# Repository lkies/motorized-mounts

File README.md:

# DIY Motorized Mirror Mounts

_Lorenz Kies <[lorenz.kies@aei.uni-hannover.de](mailto:lorenz.kies@aei.uni-hannover.de)>_

_I designed this project during my employment as a research assistant at the Institute of Gravitational Physics at Leibniz University Hannover; it is therefore intellectual property of my employer, but I have been given permission to share it under an open source license._

## Introduction

Motorized mirror mounts for guiding laser beams are already an established commercial product, but their pricing makes them unreasonable for basic automation tasks for most people. This means they are mostly reserved for applications where remote control or precise repeatable positioning is required. This is why I decided to develop a low-cost alternative for cheap automatic alignment of optical experiments. Most commercial offerings start at around $1000 per axis (including the driver), or around $4000 for a full 4-axis system required for most alignment problems. In contrast, my design can be build for under $100 for a full set, so less than $25 per axis, relying mostly on standard components and 3D printed parts. Despite the low cost, the actuator performance is competitive with lower-end commercial products and more than sufficient for most automatic alignment problems.

If you want to simply build the actuators, go to the [Instructions](#instructions) chapter. Following that, I discuss some of the [mechanical](#mechanical-design) and [electrical](#electrical-design) design considerations I made, that may be of interest to you, if you want to modify the designs. Finally, I discuss the [characterization](#characterization) experiments and metrics used to evaluate the performance of the actuators.

## Table of Contents

- [Introduction](#introduction)
- [Instructions](#instructions)
  - [Parts List](#parts-list)
  - [Actuator Assembly Instructions](#actuator-assembly-instructions)
  - [Electronics Setup](#electronics-setup)
  - [Firmware Setup](#firmware-setup)
  - [API / Software Setup](#api--software-setup)
- [Design Considerations](#design-considerations)
  - [Mechanical Design](#mechanical-design)
  - [Backlash and Hysteresis Compensation](#backlash-and-hysteresis-compensation)
  - [Electrical Design](#electrical-design)
- [Characterization](#characterization)
  - [Minimal Incremental Motion](#minimal-incremental-motion)
  - [Unidirectional Repeatability](#unidirectional-repeatability)
  - [Nonlinearity](#nonlinearity)
  - [Backlash](#backlash)
  - [Backlash Variation](#backlash-variation)
  - [Interpretation](#interpretation)
  - [Results](#results)

## Instructions

These are the instructions to build the `pancake-direct-v2` design, which is the recommended design. The other designs are mostly included for completeness' sake, if you want to build them you will have to figure it out yourself from the CAD files.

### Parts List

To build a set of **four actuators** on two **mirrors**, you will need the following parts:

| Electronic Parts | Quantity |
| - | - |
| [NEMA 14 Pancake Stepper Motor](https://www.omc-stepperonline.com/de/e-serie-runden-nema-14-bipolar-0-9deg-8ncm-11-33oz-in-1-0a-36x17mm-4-draehte-14re07-1004vrn) | 4 |
| [TMC2208 StepStick V1.2](https://aliexpress.com/item/33045459259.html) | 4 |
| [Makerbase MKS DLC32 MAX](https://aliexpress.com/item/1005008204547315.html) | 1 |
| [19V 5A Power Supply (5.5mm x 2.5mm socket)](https://de.rs-online.com/web/p/steckernetzteile/2552119) | 1 |
| [Cat7 U/FTP 2m Ethernet Cable](https://de.rs-online.com/web/p/ethernetkabel/2660713) (optional) | 2 |
| [Adapter-Board-Stepper](electrical/adapter-board-stepper) (optional) | 2 |
| [Adapter-Board-Controller](electrical/adapter-board-controller) (optional) | 2 |
| [RJ45 Socket](https://de.rs-online.com/web/p/ethernet-steckverbinder/3316443?searchId=30a561ef-d51f-4305-b438-8268e3811f80) (optional, for adapter boards) | 4 |

The links for the motors, motor drivers, and driver board are not affiliate links, they are simply the first results I found. All parts are also offered by many other suppliers. If you can not find the exact same model, you should also be able to use similar parts that perform the same function.

There are a lot of other CNC driver boards out there, many of them ESP32 based. Alternatively, it is also not too difficult to build one yourself. Similarly, you can also use different stepper drivers like the TMC2209, DRV8825 or A4988. Most stepsticks are pin compatible at least to the extent required for basic operations. If you choose to buy TMC2208 stepsticks, I recommend getting the white v1.2 version, there are many step stick designs available and some of them seem to have weird factory side configurations. Although 15V and 3.5A should technically be enough for the power supply, I recommend staying on the safe side and getting a more powerful one like the one specified. If you do not have the capabilities to manufacture PCBs, you can also buy [RJ45](https://de.aliexpress.com/item/1005004520312413.html) breakout boards instead of the custom adapter boards, or skip the Ethernet cables entirely.

| Mechanical Parts | Quantity |
| - | - |
| [MDI-HS Mirror Mount](https://www.radiant-dyes.com/index.php/products/optomechanics/high-stable-mirror-mounts/131-mdi-hs) | 2 |
| DIN 912 M2x16mm | 4 |
| DIN 934 M2 Nuts | 4 |
| DIN 912 M3x6mm | 8 |
| DIN 912 M4x12mm | 4 |
| DIN 912 M6x16mm | 2 |

In most cases, it is not necessary to use DIN 912 of these exact lengths, just use whatever is available.

| 3D Printed Parts | Material | Quantity |
| - | - | - |
| [`gear-grip.stl`](mechanical/pancake-direct-v2/gear-grip.stl) | PETG | 4 |
| [`screw-grip.stl`](mechanical/pancake-direct-v2/screw-grip.stl) | TPU 95A | 4 |
| [`fastener.stl`](mechanical/pancake-direct-v2/fastener.stl) | PETG | 4 |
| [`mount-plate.stl`](mechanical/pancake-direct-v2/mount-plate.stl) | PETG | 2 |
| [`mount-stem.stl`](mechanical/pancake-direct-v2/mount-stem.stl) | PETG | 2 |
| [`adapter-board-mount.stl`](mechanical/adapter-board/adapter-board-mount.stl) (optional) | PETG | 2 |
| [`driver-board-case-lower.stl`](mechanical/driver-board-case/driver-board-case-lower.stl) (optional) | PETG | 1 |
| [`driver-board-case-upper.stl`](mechanical/driver-board-case/driver-board-case-upper.stl) (optional) | PETG | 1 |

Other materials like PLA instead of PETG or other flexible filaments instead of TPU 95A will probably also work, this is just what I used. If you have access to a laser cutter, you can also cut the [`mount-plate.dxf`](mechanical/pancake-direct-v2/mount-plate.dxf) out of 2.5mm to 3mm thick acrylic. This is a bit stiffer and looks nicer.

### Actuator Assembly Instructions

1. Crimp a plug to the wires, make sure that the first two wires are one phase and the second two wires are the other phase, do not mix them. The polarity and positioning of the phases determine the rotation direction, but this does not really matter for most applications.
2. Insert M2 nut into `fastener`. If it does not fit, heat the nut using a lighter or soldering iron. If it does not sit tight, heat the plastic and press it together around the nut. Alternatively, hose clamps might also work well for this, but I did not test that.
3. Put the `gear-grip` on the output gear of the motor. If it is too tight, slightly bend the two halves apart. The part has a chamfer on one side that should also help with this.
4. Put the `screw-grip` on the `gear-grip`, make sure that the shallow slots in the `gear-grip` align with the shallow notches on the `screw-grip`.
5. Push the `fastener` onto the `gear-grip`, if it is too tight, slightly bend the `fastener` apart. The `fastener` has a chamfer that should mate with a very thin shoulder on the `screw-grip` to help with the alignment.
6. Before tightening the fastener, use a knife (or another thin piece of metal) to make a small gap (~0.5mm) between the motor and `gear-grip` to avoid unnecessary friction between the two.
7. Tighten the fastener using an M2x16mm screw. If the M2 nut in the `fastener` breaks free, use pliers to hold it in place while tightening.
8. Repeat steps 1-7 for the other three motors.
9. Fasten the `mount-plate` to the `mount-stem` using two M4x12mm screws. Repeat for the other mount.
10. Place two motor assemblies on their back with the wires facing inwards. (Not really necessary, but it looks nicer in my opinion.)
11. Fasten the `mount-plate` / `mount-stem` assembly onto the two motors using four M3x6mm screws. Repeat for the other mount.
12. Put a M5x16mm screw through the hole of the mirror mount that is **not** used for screwing it to its foot. Screw it in so that the head is roughly in the center of the optical axis.
13. Place the whole mirror actuator assembly onto the mirror mount and tighten the M5 screw. Repeat for the other mount. When setting up the mounts as part of a setup, I recommend doing the placement and rough alignment without the actuator assembly attached, and only attaching it for fine automatic alignment.

### Electronics Setup

1. For each of the red DIP switches between the stepstick slots, switch them all to the down/off position to select 8 microsteps per full step.
2. Plug the stepsticks into the driver board. Most stepsticks have some of the pins labeled _somewhere_ so you know which way around to plug them in.
3. If you built the adapter boards, plug them in. Beware, many CNC driver boards have two sockets for the y-axis, make sure to skip the second one.
4. **With the motors disconnected**, connect the power supply and adjust driver current reference voltage as described in the ["Motor Current Setting"](https://wiki.fysetc.com/docs/TMC2208#Motor%20Current%20Setting) section. I set it to 800 mV which indicates an RMS current of 800 mA. This may be slightly different for other stepstick designs. The drive current is a tradeoff between torque and heating. With a larger current, the motor can produce more torque and consequently move at higher speeds. However, it will also heat up faster and reach higher temperatures. The TMC2208 has an auto power-down feature that reduces the current during standstill. If you have this feature and use the motors infrequently enough, you may get away with higher currents without overheating. The motors are rated for 1.0 A per phase, so with 800 mA, should be on the safe side.
5. Attach the driver board adapters to the driver board and put the assembly in the case and close it with six DIN 912 M3x20 screws.

### Firmware Setup

1. Install Python in your preferred way.
2. Install [`esptool`](https://pypi.org/project/esptool/) for example using pip:

    ```shell
    pip install esptool
    ```

3. Download the [firmware image](firmware/firmware.bin).
4. Erase the flash memory of the controller board using:

    ```shell
    esptool --chip esp32s3 erase_flash
    ```

    If you have multiple serial devices connected, you may also need to specify the port using `--port COM[X]` on Windows or `--port /dev/ttyUSB[X]` on Linux.

5. Flash the image using:

    ```shell
    esptool --chip esp32s3 write_flash 0x0 firmware.bin
    ```

    The same note about the port applies here as well.

If you are using a different board, you will need to configure the correct pins and potentially switch the build system different architecture. You can find more details on this in the [`firmware` directory](firmware).

### API / Software Setup

1. Install Python in your preferred way.
2. Install the API package from source control using pip:

    ```shell
    pip install git+https://github.com/lkies/motorized-mounts.git#subdirectory=api
    ```

3. Control the steppers through a `StepperBoard` instance:

    ```python
    from stepper_board import StepperBoard, RpcClient, SerialBLS

    # the default baudrate of ESPs is 115200
    with SerialBLS.connect("COM[X]", 115200) as bls:
        # create proxy instance of stepper board connected to serial port
        steppers = StepperBoard(RpcClient(bls))

        # configure speed, acceleration and compensation settings
        # only needed once, the settings are saved the board's non-volatile memory
        for i in range(4):
            steppers.set_max_speed(i, 500)
            steppers.set_max_accel(i, 1e5)
            steppers.set_backlash(i, 10) # in case you want to use backlash compensation
            steppers.set_hysteresis(i, 30)
            steppers.set_compensation("hysteresis")

        # enables the stepsticks
        steppers.set_enabled(True)

        # move stepper 0 to position 1000 microsteps
        steppers.move_to(0, 1000)

        # move multiple steppers simultaneously
        steppers.move_to_vec([10, 20, 30, 40], "joint_max") 
    ```

The configuration only needs to be done once, the settings are stored on the chip's non-volatile memory and it is automatically reloaded at startup. From the characterization measurements, the backlash compensation should be about 10 microsteps at 8 microsteps per full step. The hysteresis compensation needs to be at least as large as the maximum backlash, in this case, greater than about 15 microsteps. To be on the safe side, we choose 30 microsteps. A larger hysteresis correction will cause more unnecessary extra movement, but at these small scales, it does not really matter. The best performance is achieved with hysteresis compensation, so unless you have a good reason to use backlash compensation, I would recommend using hysteresis compensation.

You can find more information about the driver boards behavior in the [`api` directory](api).

_Please consider providing feedback on the build process if you end up replicating this design so that we can optimize the instructions and the design itself. Have Fun!_

## Design Considerations

### Mechanical Design

Building a stable and robust mirror mount is not a trivial task. That is why I did not do it and instead built the design around the [MDI-HS](https://www.radiant-dyes.com/index.php/products/optomechanics/high-stable-mirror-mounts/131-mdi-hs) series mirror mounts from Radiant Dyes. They have proven themselves as reliable and stable mirror mounts in our labs. They also have slightly larger thumbscrews than other mounts, which is helpful in reducing coupling slack between them and the motor.

For the motors, I experimented with two different types of stepper motors: the extremely cheap 28BYJ-48 geared stepper motors and the slightly more expensive [Nema 14 Pancake motors](https://www.omc-stepperonline.com/de/e-serie-runden-nema-14-bipolar-0-9deg-8ncm-11-33oz-in-1-0a-36x17mm-4-draehte-14re07-1004vrn) (400 step/rev version). The 28BYJ-48 motors are normally unipolar stepper motors, but they are not too difficult to [modify for bipolar operations](https://ardufocus.com/howto/28byj-48-bipolar-hw-mod/). This has two advantages: first, bipolar operation is not limited to using half the coil windings, which means more torque. Second, and much more importantly, it is much easier to get good microstepping drivers for bipolar motors, such as the TMC2208. This is very important because the excess vibration caused by bad drivers causes a lot of problems with sensitive optical experiments.

One simple method for increasing the actuation resolution of an actuator is to use a gear reduction. However, this may not always lead to better performance since the gearing also introduces backlash and other hysteresis-like effects. To investigate this, I designed a geared and a direct drive version for both motors. Typically, gearboxes, especially stiff metal gears, are intentionally designed with some slack to prevent jamming and allow for lubrication, but this also means that they will have backlash. Without this play, even tiny manufacturing tolerances can reduce the slack "below zero" which then requires strong deformation forces to move past, if possible at all. This is not as critical in plastic gears, which allow for more deformation. In fact, we can deliberately introduce radial compliance in the gear, which then allows us to preload them without the risk of jamming and excessive required forces to move. With this, we can effectively eliminate backlash, but the compliance itself may introduce other hysteresis-like effects.

Another challenge is to provide a reliable coupling between the motor and the mount. While a form fit is generally good for preventing slippage, it requires precise manufacturing to match the mating part. In addition to that, the stiff coupling requires the axis of the mount to be very well aligned with the axis of the motor, otherwise the mechanism may not be able to move freely. Because of these reasons, I choose to use a friction fit with TPU 95A, providing the required compliance. This has a few advantages, firstly, the compliance allows for slight radial misalignments by deforming. The knurled knob provides good grip for torque transfer while still allowing for some axial slip to deal with the screw moving in and out of the mount as it is actuated. And finally, it is easy to manufacture on most 3D printers and does not require additional elements like grub screws. The major disadvantage is that there will be additional hysteresis-like effects. In practice, this does not seem to be very severe, although it is possible that it is currently a limiting factor on the minimal incremental motion.

### Backlash and Hysteresis Compensation

While there is only one way for an actuator to be "perfect", i.e. a simple linear mapping from desired position to actual mirror orientation, there are many ways in which an actuator can be imperfect. Here is a list of the types of imperfections investigated and possible compensation approaches. You can find more details about how we characterized them in the [Characterization](#characterization) section.

- Minimal Incremental Motion: This is the smallest unidirectional change in position that the actuator can reliably produce. Changes in input that are smaller have no meaningful effect on the output due to digital resolution limits, stick-slip effects or limitations in the drive train.
- Backlash: It is commonly defined as "the maximum distance or angle through which any part of a mechanical system may be moved in one direction without applying appreciable force or motion to the next part in mechanical sequence." For our purposes, we can define it as the additional change in input we need to apply after a direction change before the output starts to change. If this is consistent, it can be compensated for by adding that amount to the input when changing direction.
- Backlash Variability: If the backlash is not consistent over the actuator's range of movement, it can not be compensated for with simple backlash compensation. However, if it is consistent for a given position, we can compensate for it by always approaching the desired position from the same direction. With this approach, we can also compensate for any other hysteresis-like effects, so we will call it hysteresis compensation as opposed to the simple backlash compensation. Hysteresis compensation is generally more robust and leads to better accuracy because it compensates for more imperfections and does not require precise knowledge of the backlash. However, it is slower since it requires extra movement to approach the desired position from the correct direction.
- Macroscopic Nonlinearity: Besides the small-scale nonlinear behavior described by the minimal incremental motion, there may also be macroscopic nonlinearities due to non-ideal components in later stages of the transmission. These could be compensated for by calibrating them out, but this is generally not necessary for automatic alignment applications where precise repeatable movement is much more critical.

### Electrical Design

The stepper motors are a crucial part for providing precise, repeatable actuation. To get the best performance out of them, it is important to use good stepper drivers. I chose the TMC2208 drivers because of their quiet and vibration free stealth chop mode to avoid disturbing sensitive optical experiments, but other drivers might also be good enough and are usually pin compatible if integrated onto a stepstick. To drive them I used an ESP32 (old or S-series) because of their high resolution timers and established ecosystem. While it is not too hard to design a PCB that connects the microcontroller to the four stepsticks, it is superfluous because this kind of problem has been solved many times before for CNC machines, 3D printers and laser cutters. There are a lot of these boards out there, and quite a few of them even use the ESP32 based controllers. I selected the Makerbase MKS DLC32 MAX V1.2 because it is compact and cheap (<20€ on AliExpress) and has the required four stepper driver slots and ESP32s3 controller. Sadly, the schematics are not open source, but the [pinout](https://github.com/user-attachments/files/19184922/MKS.DLC32.MAX.V1.0_002.PIN.pdf) can be found online.

I wrote my own firmware that implements speed and acceleration limits, as well as backlash and hysteresis compensation, with a simple JSON-based serial interface to control it. But it might be interesting to investigate using established software like [GRBL](https://github.com/grbl/grbl) to simplify the project even further.

While the motors I used do not require much power, I would still recommend using a power supply with more than 15V. At high speeds, the inductance becomes the limiting factor in how much current can flow. If the driver has a higher voltage supply, it can change the current through the inductor faster to maintain reasonable torque at high speeds. But be careful setting the current limit on the drivers, they can easily overheat and potentially damage the 3D printed parts.

Since you will most likely not want to mount the controller board on your optical table, you will need to extend the motor wires somehow. For this, I recommend using Ethernet cables. With four twisted pairs, a single Ethernet cable can drive two stepper motors, enough for the two axes of a single steering mirror. Another advantage of using Ethernet cables is that they also shield the individual motor wire pairs preventing electromagnetic interference from the comparatively high drive currents. While more shielding might sound attractive, especially considering the current going through these wires, I still recommend using U/FTP cables because they are typically much more flexible than cables with overall shielding. To go from the driver board to RJ45 and back at the mirrors, we use custom adapter boards, but you can also buy RJ45 breakout boards if you do not have the capability to make your own.

## Characterization

To measure the performance of the actuators, we use one simple experiment and multiple evaluations to extract the quantities of interest from the data. The experimental setup is very straightforward, we shine a laser beam at the mirror of the mount to be evaluated and then measure the changes in position on a screen. The position which is approximately proportional to the change in mirror angle is measured using the difference voltage of a four quadrant photodetector, while this is not linear in the position, the nonlinearity is easy to calibrate out. We then move the actuator back and forth multiple times and record the input and measured output position. After each movement, we wait for 100 ms for the mount and table to settle to get as precise a measurement as possible. All performance metrics are then derived from this data.

Example code for computing the quantities can be found in the [plotting notebook](images/plots/plots.ipynb). The actual code used is slightly different and can be found in the [evaluation module](characterization/evaluation.py). To better illustrate the individual effects, the example plots shown are based on simulated data which is also generated in the plotting notebook.

### Minimal Incremental Motion

In a loose sense, the minimal incremental motion is the smallest change in input, that reproducibly leads to a change in output. To quantify it we look at small segments of the unidirectional travel, where other nonlinearities are negligible. We compute the mean expected movement using a unity slope linear regression line and then look at the distribution of the residuals. Ideally, the span of the distribution i.e. max - min then gives us the minimal change in input that we need to apply to get a reliable change in output. In practice, the measurements are subject to noise and so maximum and minimum values are most likely outliers which are not representative of the expected performance. We can mitigate this by only looking at the inner $x$ percent of values. For example if we want to take the inner 95% of values we use the 2.5th and 97.5th percentile instead of the minimum and maximum.

We can get estimates of the confidence intervals by bootstrapping the distribution of residuals.

<image src="images/plots/min_increment.png" alt="Minimal Incremental Motion Plot" width="400px"/>

The plot shows minimal incremental motion limited by stick slip effects. For most small changes in input, the system "sticks" and the changes in output are purely noise. Once the input change is large enough, the system "slips" and the output changes suddenly. Because of this, the system can not be controlled at scales finer then the "steps" of the slips.

### Unidirectional Repeatability

In addition to the mostly consistent stick-slip effects that limit the minimal incremental motion, there may be other randomized effects that cause the actuator's output to differ between multiple repetitions of the same input. We call this unidirectional repeatability. This is in contrast to bidirectional repeatability, which is usually limited by backlash and backlash variation. We determine it by examining the peak-to-peak deviation in output across multiple repetitions of the same input, while accounting for movement direction. And again, to account for measurement noise, we do not use the maximum and minimum values but instead use percentiles for greater robustness against noise and outliers. By only comparing against points with the same input and direction as opposed to a linear regression line, this metric is independent of nonlinearity or backlash.

<image src="images/plots/unidirectional_repeatability.png" alt="Unidirectional Repeatability Plot" width="400px"/>

Moving through the same segment multiple times, we see that the output randomly ends up in slightly different positions, limiting the achievable accuracy.

### Nonlinearity

Ideally, after accounting for backlash and minimal incremental motion, there should be a linear relationship between input and output position. In practice, this might not be the case due to manufacturing tolerances across various parts of the drive train. To quantify this, we look at motion across a large segment of the travel and compute the residuals to a linear regression. Similar to minimal incremental motion, instead of directly using the minimum and maximum values, we use percentiles to mitigate the effects of outliers.

<image src="images/plots/nonlinearity.png" alt="Nonlinearity Plot" width="400px"/>

The input-output relationship is not perfectly linear. A user or application that assumes linear behavior will see a systematic deviation from the expected output corresponding to the nonlinearity.

### Backlash

In general, hysteresis is the dependence of a system's state on its history. In the context of actuators, this usually means whether we previously moved the actuator in the same direction or not. In more complicated cases, the behavior may also depend on how long ago the last change in direction was. The dominant source of hysteresis effects in mechanical systems is usually backlash. It is the consequence of play in the force-transmitting elements of the actuator. When we change direction, parts with play need to move through a dead zone before they make contact again and start transmitting force. We defined backlash as the additional movement we need to apply to the actuator after changing direction before the output begins to change.

To determine the backlash from measured data, we can perform a virtual backlash compensation during measurement post-processing. For this, we split all movement segments into forward and backward motion. Then we then shift the recorded input values of the backwards motion by the amount of backlash to compensate for. Finally, we delete the datapoints in the dead zone after changes in direction. We define the backlash as the compensation value that maximizes overlap between the forward and backward segments. In the process, we also get backlash-compensated data that we can use for other evaluations.

Alternatively, we can also determine the backlash as the negative of the signed integral of the hysteresis loop in the input-output space relative to the maximum change in output position (i.e. change in input minus backlash). The advantage of this method is that it does not require a metric to compute the overlap between forward and backward segments. The downside is that we always need to integrate over full hysteresis loops to get valid results. Additionally, we also do not get backlash compensated data for other evaluations.

In both of these evaluations, we compute the backlash in terms of the input position. However, we are usually interested in the backlash in terms of output position. For this, we just multiply it by the input-output proportionality.

It is important to note that it is a matter of convention that we choose the forward direction to be the true direction and the backward direction to be the one affected by backlash. We could just as easily select the backward direction to be the true direction or any mix of the two and split the backlash compensation between the two. However, there is an output offset between the different conventions. The driver board considers the forward direction to be the true direction and applies the backlash compensation to the backward direction, so we stick to this convention for consistency.

We can get confidence intervals by computing the backlash for each cycle individually and then using standard t-statistic-based confidence intervals.

<image src="images/plots/backlash.png" alt="Backlash Plot" width="400px"/>
When changing direction, there is a dead zone before the output starts to change again. This means that the output position is consistently to hight when moving backwards. By shifting the recorded input values for all backwards motion and cutting out the dead zone after direction changes, the forward and backward trajectories overlap again.

### Backlash Variation

While constant backlash is not too difficult to compensate for by adding a constant bias after a direction change, this does not work for variable backlash. In that case, compensating for an average backlash will lead to overcompensation in some cases and undercompensation in others. Quantifying this is somewhat messier than the other metrics, as we need a way to determine the local backlash. To get a reasonable estimate of the local backlash, we need to be able to determine the input deviation between the forward and backwards trajectories for the same output positions. To provide a balance between resolution and smoothing, we interpolate using a Gaussian kernel with a bandwidth equal to the average spacing between consecutive outputs. We then collect all deviations between forward and interpolated backwards or backwards and interpolated forward trajectories. From these deviations we can then again compute lower and upper quantiles to get noise-robust estimates of the differences between maximum and minimum values.

<image src="images/plots/backlash_variation.png" alt="Backlash Variation Plot" width="400px"/>

The backlash is not consistent across the range of movement. After compensating for the average backlash, the range with small backlash is overcompensated and the range with large backlash is undercompensated. This leads to a systematic deviation from the expected output that depends on the position of the actuator.

### Interpretation

An obvious question that arises when looking at these metrics and comparing different motors is, which of these metrics actually matter? The annoying answer here is, it depends on the application and the compensation mode or lack thereof, that is used. For this, we need to introduce the terms of accuracy and precision, which we will call repeatability, to avoid confusion with accuracy. Accuracy describes the deviation of the _expected_ output (i.e., averaged across many iterations) from the true (linear) relation, or, in a looser sense, whether the average output is correct. Precision or repeatability describes the deviation of individual measurements between multiple repetitions of the same input, or in a looser sense, is the actuator consistent. So accuracy or lack thereof is a matter of systematic errors, while repeatability is a matter of random errors. Even though backlash and backlash variation are technically deterministic, we will treat them as random errors for measures of repeatability, as they can appear random to a user or algorithm that is not aware of the history of the actuator.

With this, we can specify the expected performance for different compensation modes. The specified values are bounds for worst-case deviations, discounting errors from noisy measurements and extreme outliers (because we used percentiles instead of maximum and minimum values). We assume that the backlash compensation is applied with the median backlash (between minimum and maximum variation) and that the hysteresis compensation is applied with at least the maximum backlash.

| Compensation Mode       | Remaining (In-)Accuracy                      | Remaining (Un-)Repeatability                                                              |
|-------------------------|----------------------------------------------|-------------------------------------------------------------------------------------------|
| None                    | Backlash + Backlash Variation + Nonlinearity | Backlash + Backlash Variation + Unidirectional Repeatability + Minimal Incremental Motion |
| Backlash Compensation   | Backlash Variation + Nonlinearity            | Backlash Variation + Unidirectional Repeatability + Minimal Incremental Motion            |
| Hysteresis Compensation | Nonlinearity                                 | Unidirectional Repeatability + Minimal Incremental Motion                                 |

If we define the ground truth to lie between the most extreme positive and negative deviations, the actual accuracy and repeatability will be half the values specified.

Depending on the application, either the accuracy or repeatability may be more important. For example, for auto-alignment applications using hysteresis compensation, the nonlinearity will effectively distort the observed figure of merit in terms of the input. As long as this distortion is small enough, this should not matter to the optimizer which mostly cares about repeatability.

Overall, the best performance is achieved with hysteresis compensation, and it should therefore be the default choice for most applications. The only downside compared to backlash compensation is that it leads to additional movement to always approach the desired position from the same side. This makes actuation slower, especially if most movements are smaller than the hysteresis compensation value.

### Results

At the time of performing the characterization measurements, we also had two commercial models from Newport available, which they had kindly lent us for evaluation. The [TRA6CC](https://www.newport.com/p/TRA6CC) designated as `newport-dc` is a closed loop DC motor, the [TRA6PPD](https://www.newport.com/p/TRA6PPD) designated as `newport-stepper` is an open loop stepper motor based design.

The characterization experiments were performed with the following parameters:

- Short evaluation range: $5\text{ mdeg}$ (Used for minimal incremental motion)
- Long evaluation range: $50\text{ mdeg}$ (Used for all other evaluations)
- Number of cycles for short stroke high resolution measurements: $10$
- Number of cycles for long stroke measurements: $5$
- Evaluation quantile for noise robust min max estimates: $95\%$ (i.e. 2.5th and 97.5th percentiles)
- Confidence interval: $95\%$ (rounded up to larger deviation for asymmetric intervals)
- Bootstrap samples: $10 000$

The actual stroke lengths varied between the different motors, but they were all larger than the evaluation range.

| Actuator Model    | 95% min. inc (µdeg)   | 95% uni. rep. (µdeg)   | 95% nonlin. (µdeg)   | backlash (µdeg)   | 95% BL var. (µdeg)   |
|:------------------|----------------------:|-----------------------:|---------------------:|------------------:|---------------------:|
| `cheap-geared`    | 521 ± 27              | 490 ± 19               | 1034 ± 23            | 2763 ± 116        | 507 ± 19             |
| `cheap-direct`    | 490 ± 39              | 2014 ± 131             | 923 ± 44             | 4420 ± 590        | 2007 ± 132           |
| `pancake-geared`  | 445 ± 18              | 1144 ± 25              | 803 ± 40             | 1620 ± 768        | 1154 ± 20            |
| `pancake-direct`  | 503 ± 33              | 614 ± 21               | 613 ± 20             | 1543 ± 170        | 622 ± 20             |
| `newport-dc`      | 285 ± 15              | 534 ± 18               | 587 ± 18             | 10692 ± 105       | 539 ± 17             |
| `newport-stepper` | 298 ± 16              | 441 ± 17               | 533 ± 16             | 10049 ± 63        | 459 ± 14             |

The uncertainty estimates provided are purely derived from statistical data and do therefore not account for systematic errors. For example, the `cheap-direct` instance was probably built using an unusually bad motor since it has significantly more backlash variation and repeatability than the geared version. Even with a perfect gear reduction, the direct-drive version should only be three times as bad as the geared version.

It is interesting to note that all DIY designs have roughly the same minimal incremental motion. This suggests that it is not limited by the motor or gear reduction but rather by the parts they share in common. The most likely candidate for this is the TPU friction fit coupling, but it is also possible that it is the threading in the mirror mount. To put this into context, $500\text{ µdeg}$ in rotation corresponds to about $270\text{ nm}$ of screw translation, which is already impressively small for something based on metal sliding on metal.

Overall, the `pancake-direct` design has the best overall performance of the DIY designs, while also being the simplest to build. It is still beaten by the commercial models in terms of minimal incremental motion, but it has very similar performance in terms of repeatability, nonlinearity and backlash variation. The backlash itself is significantly better than the commercial models, although this does not necessarily provide an advantage in practice since backlash is easily compensated. However, it does make hysteresis compensation more feasible since the extra movement required to approach the desired position from the correct direction is smaller. It is worth noting that the Newport motors were at a slight advantage due to their larger mirror mount lever of $40\text{ mm}$ compared to $31\text{ mm}$ for the DIY designs.

If more accurate actuation is required, the Radiant Dyes mirror mounts are also available with $100\text{ µm/rev}$ screw pitch as opposed to the $250\text{ µm/rev}$ used here. Depending on what the limiting factors are, this might provide **up to** a 2.5-fold reduction in all metrics, leading to minimal incremental motions around $200\text{ µdeg}$.

There are also notable differences between the DIY and commercial models that these metrics do not capture. Most importantly, the commercial models have homing capabilities while the DIY motors do not. However, for automatic alignment applications, which was the main motivation for building these motors, the loop is closed by the figure of merit, and homing is therefore not really necessary and more of a convenience feature. Another advantage of the commercial models is that they move faster, although we made no comprehensive quantitative measurements to compare this in detail. On the other hand, the DIY motors have two important practical advantages. First, they can easily be attached to existing mounts without changing their position. This also means they can easily be removed for manual prealignment which is much more convenient than having to steer them through control software on a computer. Secondly, they are much more compact, which makes the mirrors they are attached to easier to handle and also allows for placement in much tighter places.

And finally, they are of course **much** cheaper with less than 3% of the cost of commercial models.

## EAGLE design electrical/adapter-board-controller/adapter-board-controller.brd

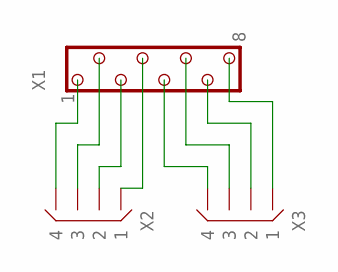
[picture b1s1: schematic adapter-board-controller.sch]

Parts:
X1: XS08-RJ45; XS08-2S-RJ45
X2, X3: X04; X04-SIL-MALE-VERT-L

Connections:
unnamed: X1.4, X2.1
unnamed: X1.3, X2.2
unnamed: X1.2, X2.3
unnamed: X1.1, X2.4
unnamed: X1.5, X3.4
unnamed: X1.6, X3.3
unnamed: X1.7, X3.2
unnamed: X1.8, X3.1

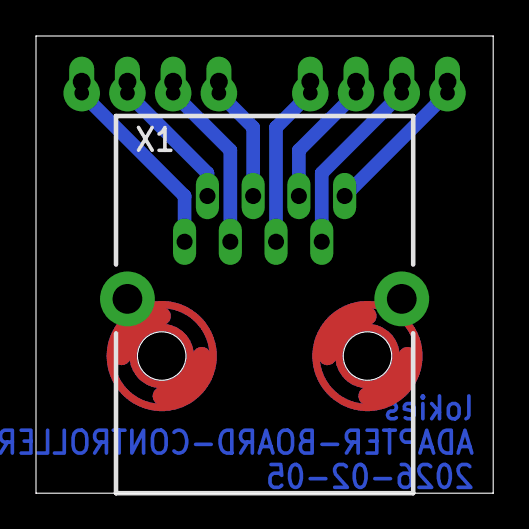
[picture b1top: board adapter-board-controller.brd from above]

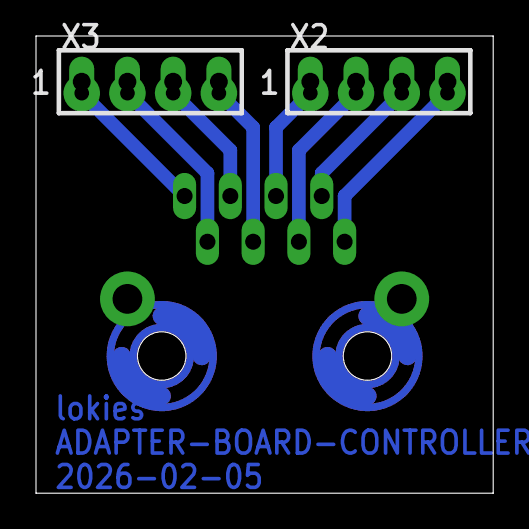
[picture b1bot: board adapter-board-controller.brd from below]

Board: 2 copper layers, 25.4 x 25.4 mm, 4 parts (3 on the bottom side), 8 nets.

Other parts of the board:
U$2: INFO-SMALL

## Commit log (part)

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2026-04-02 cleaned initial commit
2026-04-07 add serial to tcp forwarding for enable remote connections
2026-05-20 change field names in rpc protocol to make it compatible with jsonrpc
